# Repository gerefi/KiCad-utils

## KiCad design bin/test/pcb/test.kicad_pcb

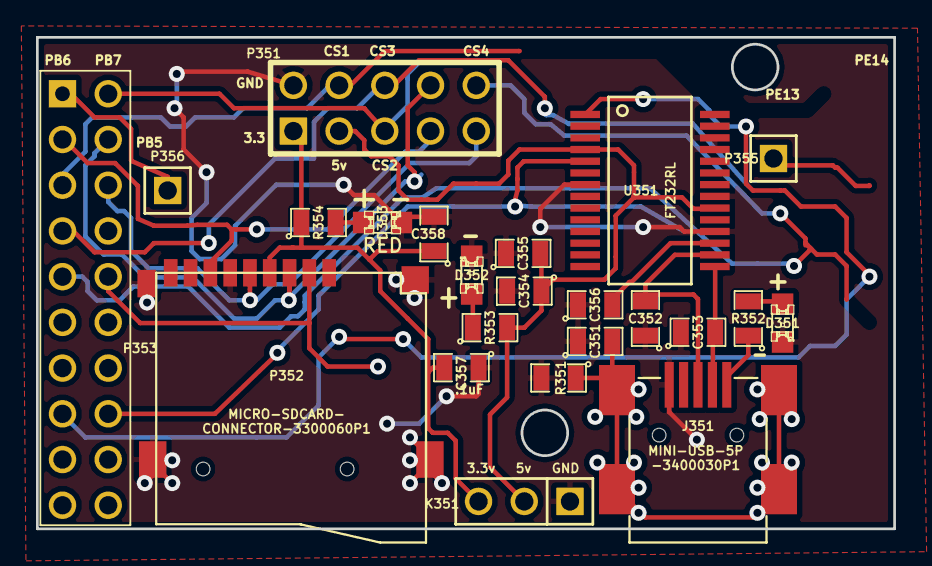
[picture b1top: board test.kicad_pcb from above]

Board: 2 copper layers, 47.6 x 27.3 mm, 24 parts (1 on the bottom side), 22 nets.

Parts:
C351: 4700pF; SM0805
C352, C353: 47pF; SM0805
C354, C358: 4.7uF; SM0805
C355, C356, C357: .1uF; SM0805
D351: GREEN; LED-0805
D352, D353: RED; LED-0805
G305: LOGO; LOGO_F
J351: MINI-USB-5P-3400020P1
K351: CONN_3; PIN_ARRAY_3_A
P351: CONN_5X2; PIN_ARRAY_5x2
P352: MICRO-SDCARD-CONNECTOR-3300060P1
P353: CONN_10X2; PIN_ARRAY_10X2
P355, P356: CONN_1; PIN_ARRAY_1
R351: 1M; SM0805
R352, R353, R354: 1k; SM0805
U351: FT232RL; ssop-28

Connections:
/3.3V: C357.2, C358.1, K351.3, P351.1, P352.4, R354.1
/5V: C354.1, C355.2, K351.2, P351.3, R353.2, U351.4, U351.20
/CAN_TX: P353.1, P356.1
/CS1: P351.4, P353.5
/CS2: P351.5, P353.2
/CS3: P351.6, P353.7
/CS4: P351.10, P353.9
/CS_SD_MODULE: P352.2, P353.10
/SPI_MISO: P351.7, P352.7, P353.3
/SPI_MOSI: P351.8, P352.3, P353.4
/SPI_SCK: P351.9, P352.5, P353.6
/USART_RX: P353.16, U351.5
/USART_TX: P353.15, U351.1
GND: C351.1, C352.1, C353.1, C354.2, C355.1, C356.1, C357.1, C358.2, D351.2, D352.2, D353.2, J351.5, K351.1, P351.2, P352.6, P352.G301, P352.G302, P352.G303, P352.G304, R351.2, U351.7, U351.18, U351.21, U351.25, U351.26
unnamed: J351.1, R352.1
unnamed: C351.2, J351.6, R351.1
unnamed: C353.2, J351.2, U351.15
unnamed: D351.1, R352.2
unnamed: C356.2, U351.17
unnamed: D352.1, R353.1
unnamed: C352.2, J351.3, U351.16
unnamed: D353.1, R354.2

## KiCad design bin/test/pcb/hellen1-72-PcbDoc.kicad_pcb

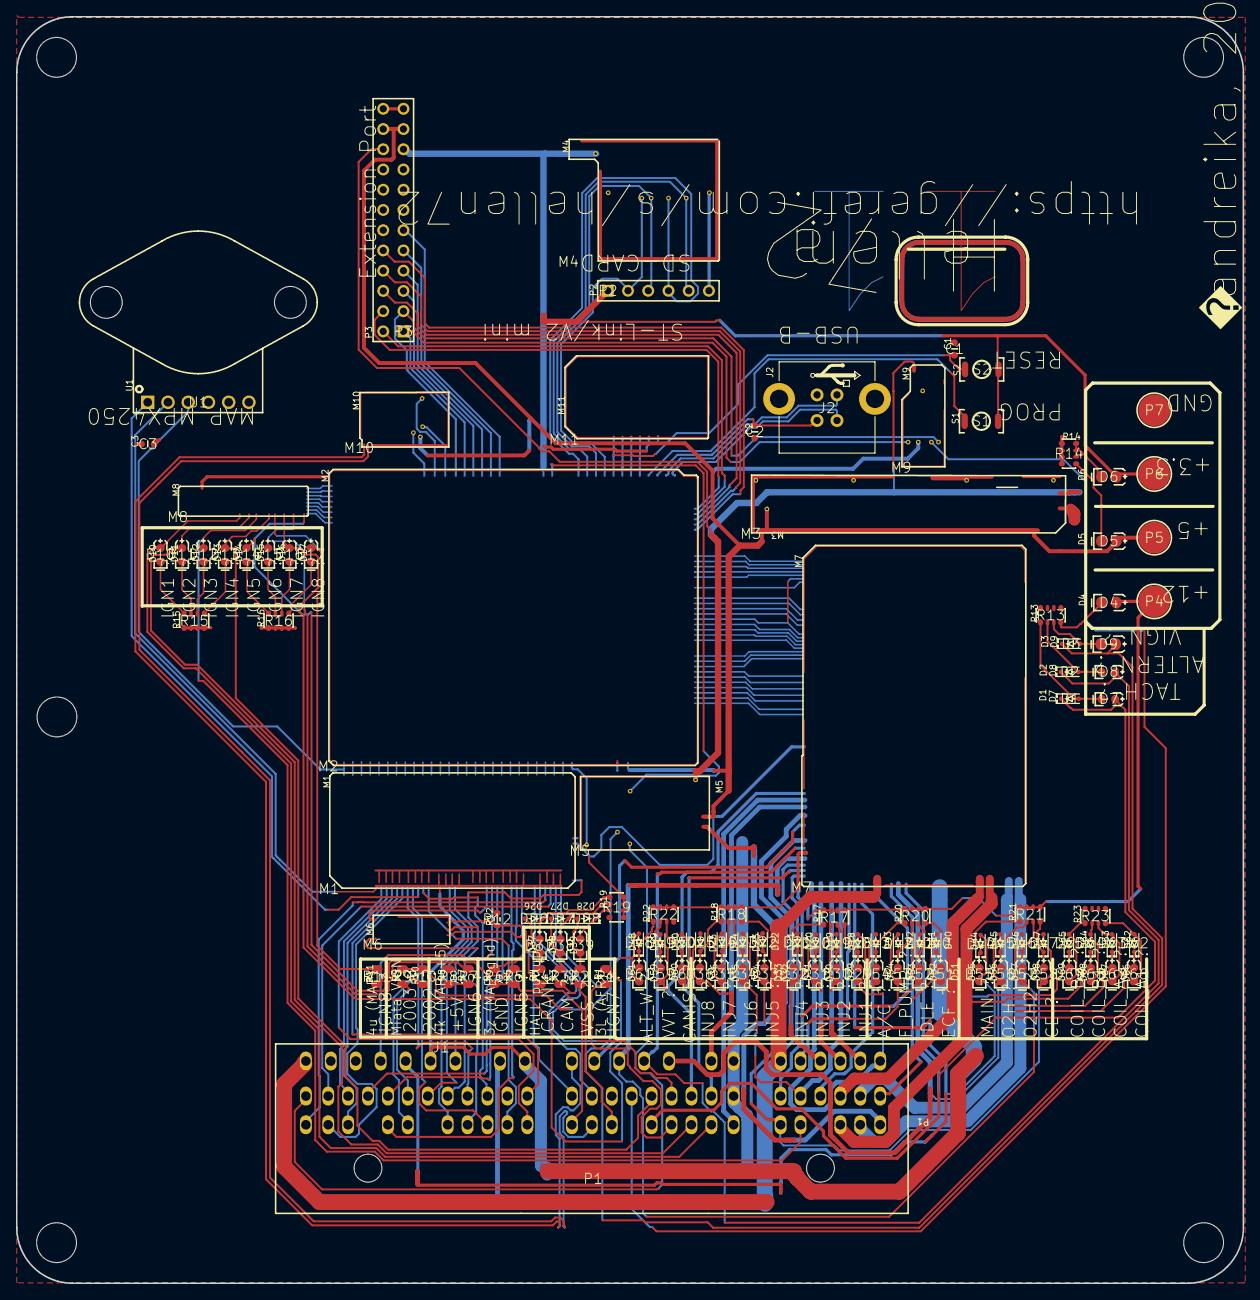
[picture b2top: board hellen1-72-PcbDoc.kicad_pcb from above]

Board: 2 copper layers, 154.0 x 159.0 mm, 118 parts (0 on the bottom side), 204 nets.

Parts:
C1: C1; C0603
C2: C2; C0603
C3: C3; C0603
D1: D1; SOD-323
D2: D2; SOD-323
D3: D3; SOD-323
D4: D4; LED-0805
D5: D5; LED-0805
D6: D6; LED-0805
D7: D7; LED-0603
D8: D8; LED-0603
D9: D9; LED-0805
D10: D10; LED-0603
D11: D11; LED-0603
D12: D12; LED-0603
D13: D13; LED-0603
D14: D14; LED-0603
D15: D15; LED-0603
D16: D16; LED-0603
D17: D17; LED-0603
D18: D18; SOD-323
D19: D19; SOD-323
D20: D20; SOD-323
D21: D21; SOD-323
D22: D22; SOD-323
D23: D23; SOD-323
D24: D24; SOD-323
D25: D25; SOD-323
D26: D26; SOD-323
D27: D27; SOD-323
D28: D28; SOD-323
D29: D29; LED-0603
D30: D30; LED-0603
D31: D31; LED-0603
D32: D32; LED-0603
D33: D33; LED-0603
D34: D34; LED-0603
D35: D35; LED-0603
D36: D36; LED-0603
D37: D37; LED-0603
D38: D38; LED-0603
D39: D39; LED-0603
D40: D40; SOD-323
D41: D41; SOD-323
D42: D42; SOD-323
D43: D43; SOD-323
D44: D44; SOD-323
D45: D45; SOD-323
D46: D46; SOD-323
D47: D47; SOD-323
D48: D48; SOD-323
D49: D49; SOD-323
D50: D50; SOD-323
D51: D51; LED-0603
D52: D52; LED-0603
D53: D53; LED-0603
D54: D54; LED-0603
D55: D55; LED-0603
D56: D56; LED-0603
D57: D57; LED-0603
D58: D58; LED-0603
D59: D59; LED-0603
D60: D60; LED-0603
D61: D61; LED-0603
D62: D62; SOD-323
D63: D63; SOD-323
D64: D64; SOD-323
D65: D65; SOD-323
D66: D66; LED-0603
D67: D67; LED-0603
D68: D68; LED-0603
D69: D69; LED-0603
J1: J1; NET-TIE
J2: J2; CONN-USB-B-VERTICAL
M1: M1; MOD_Hellen_Input
M2: M2; MOD_Hellen_MCU
M3: M3; MOD_Hellen_POWER_5
M4: M4; MOD_HELLEN_SD
M5: M5; MOD_Hellen_POWER_12
M6: M6; MOD_Hellen_Knock
M7: M7; MOD_Hellen_OUTPUT
M8: M8; MOD_Hellen_IGN8
M9: M9; MOD_Hellen_LIN
M10: M10; MOD_Hellen_CAN
M11: M11; MOD_HELLEN_STLINK
P1: P1; CONN-TE-72-PIN
P2: P2; HDR1X6
P3: P3; HDR2X12
P4: P4; PAD-SMD-4.0
P5: P5; PAD-SMD-4.0
P6: P6; PAD-SMD-4.0
P7: P7; PAD-SMD-4.0
R1: R1; R0805
R2: R2; R0805
R3: R3; R0805
R4: R4; R0805
R5: R5; R0805
R6: R6; R0805
R7: R7; R0805
R8: R8; R0805
R9: R9; R0805
R10: R10; R0805
R11: R11; R0805
R12: R12; R0603
R13: R13; R0603_x4
R14: R14; R0603_x4
R15: R15; R0603_x4
R16: R16; R0603_x4
R17: R17; R0603_x4
R18: R18; R0603_x4
R19: R19; R0603_x4
R20: R20; R0603_x4
R21: R21; R0603_x4
R22: R22; R0603_x4
R23: R23; R0603_x4
S1: S1; BUTTON-SKRK
S2: S2; BUTTON-SKRK
U1: U1; MPX4250AP

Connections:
AC: M2.E9, M7.W37
AC_PRESS: M1.N10, M2.S24
AFR: M1.N26, M2.S8
ALTERN: M2.E19, M7.W28
ALT_WARN: M2.E7, M7.W39
BOOT0: M2.N26, S1.1
BRAKE: M1.N6, M2.S28
CAM: M1.N19, M2.S15
CAM_PULLUP: D27.2, D38.2, R3.2
CANIST: M2.E21, M7.W26
CAN_N: M10.S1, P1.3X
CAN_P: M10.S2, P1.3W
CAN_RX: M2.N2, M10.V6
CAN_TX: M2.N3, M10.V5
CAN_VIO: M2.N1, M10.V2
CE: M2.E22, M7.W25
CLT: M1.N16, M2.S18
CLUTCH: M1.N8, M2.S26
COIL_A1: M2.E14, M7.W33
COIL_A2: M2.E15, M7.W32
COIL_B1: M2.E16, M7.W31
COIL_B2: M2.E17, M7.W30
CRANK: M1.N21, M2.S13
CRANK_PULLUP: D26.2, D37.2, R4.2
ECF: M2.E28, M7.W21
EGR: M1.N11, M2.S23
EXT_IO1: M2.N6, P3.5
EXT_IO2: M2.N7, P3.7
EXT_IO3: M2.N8, P3.9
EXT_IO4: M2.N9, P3.11
EXT_SPI_CS1: M2.E4, P3.8
EXT_SPI_CS2: M2.E5, P3.10
EXT_SPI_MISO: M2.E2, P3.2
EXT_SPI_MOSI: M2.E3, P3.6
EXT_SPI_SCK: M2.E1, P3.4
FTP_PPS: M1.N5, M2.S29
FUEL_LEVEL: M1.N24, M2.S10
GND: C1.2, C2.1, J1.1, J2.4, M1.E1, M1.E5, M2.S2, M3.E1, M3.V1, M3.V2, M3.V3, M3.V4, M4.G, M4.V2, M4.V3, M5.S1, M7.G, M7.S3, M8.G, M9.E1, M9.S1, M10.E1, M11.G, P1.3A, P1.3B, P1.4A, P2.6, P3.23, P3.24, P7.1, R13.5, R13.6, R13.7, R13.8, R14.5, R14.6, R14.7, R14.8, R15.5, R15.6, R15.7, R15.8, R16.5, R16.6, R16.7, R16.8, R23.5, R23.6, R23.7, R23.8
GNDA: C3.2, J1.2, M1.J2, M1.J11, M1.J12, M1.J13, M1.J14, M1.J22, M1.J23, M1.J25, M1.J26, M1.N2, M2.S32, M6.E1, P1.4O, R6.2, R12.1, U1.2
IAT: M1.N15, M2.S19
IDLE: M2.E18, M7.W29, M7.W35
IGN1: M2.W1, M8.E8
IGN2: M2.W2, M8.E7
IGN3: M2.W3, M8.E6
IGN4: M2.W4, M8.E5
IGN5: M2.W5, M8.E4
IGN6: M2.W6, M8.E3
IGN7: M2.W7, M8.E2
IGN8: M2.W8, M8.E1
INJ1: M2.E25, M7.W24
INJ2: M2.E26, M7.W23
INJ3: M2.E29, M7.W20
INJ4: M2.E30, M7.W19
INJ5: M2.E31, M7.W18
INJ6: M2.E32, M7.W17
INJ7: M2.E33, M7.W16
INJ8: M2.E34, M7.W15
IN_AC_PRESS: M1.S17, P1.4F
IN_AFR: M1.S1, P1.3L, R1.1
IN_BRAKE: M1.S23, P1.4B
IN_CAM: M1.S5, P1.3V, R3.1
IN_CLT: M1.S15, P1.4P
IN_CLUTCH: M1.S20, P1.4I
IN_CRANK: M1.S8, P1.3Y, R4.1
IN_EGR: M1.S22, P1.4AE
IN_FTP_PPS: M1.S24, P1.4AB
IN_FUEL_LEVEL: M1.S3, P1.4AD
IN_IAT: M1.S16, P1.4N
IN_KNOCK: M1.S7, M6.E3
IN_KNOCK_RAW: M6.W1, P1.4M
IN_MAF: M1.S11, P1.4X, R12.2
IN_MAP2: M1.S12, P1.4U, R11.1
IN_MAP3: M1.S19, U1.1
IN_NEUTRAL: M1.S18, P1.4H
IN_O2S: M1.S9, P1.4W
IN_O2S2: M1.S25, P1.4AA
IN_SENS2: M1.S2, P1.3K
IN_SENS4: M1.S4, P1.4AH
IN_STEERING: M1.S26, P1.4C
IN_TPS: M1.S10, P1.4V
IN_VIGN: D3.1, D9.1, M5.V3, R9.2, R10.2
IN_VSS: M1.S6, P1.3T, R2.1
IN_VTCS: M1.S21, P1.4J
KNOCK: M1.N22, M2.S12
LIN: M9.V4, P1.3Q
MAF: M1.N14, M2.S20
MAIN: M2.E6, M7.W40
MAP2: M1.N13, M2.S21
MAP3: M1.N12, M2.S22
NEUTRAL: M1.N9, M2.S25
NetD1_2: D1.2, D7.2, R13.1
NetD2_2: D2.2, D8.2, R13.2
NetD3_2: D3.2, D9.2, R13.3
NetD4_2: D4.2, R13.4
NetD5_2: D5.2, R14.1
NetD6_2: D6.2, R14.2, R14.3, R14.4
NetD10_2: D10.2, R15.4
NetD11_2: D11.2, R15.3
NetD12_2: D12.2, R15.2
NetD13_2: D13.2, R15.1
NetD14_2: D14.2, R16.4
NetD15_2: D15.2, R16.3
NetD16_2: D16.2, R16.2
NetD17_2: D17.2, R16.1
NetD18_1: D18.1, D29.1, R17.4
NetD19_1: D19.1, D30.1, R17.3
NetD20_1: D20.1, D31.1, R17.2
NetD21_1: D21.1, D32.1, R17.1
NetD22_1: D22.1, D33.1, R18.4
NetD23_1: D23.1, D34.1, R18.3
NetD24_1: D24.1, D35.1, R18.2
NetD25_1: D25.1, D36.1, R18.1
NetD26_1: D26.1, D37.1, R19.1
NetD27_1: D27.1, D38.1, R19.2
NetD28_1: D28.1, D39.1, R19.3
NetD40_1: D40.1, D51.1, R20.4
NetD41_1: D41.1, D52.1, R20.3
NetD42_1: D42.1, D53.1, R20.2
NetD43_1: D43.1, D54.1, R20.1
NetD44_1: D44.1, D55.1, R21.1
NetD45_1: D45.1, D56.1, R21.2
NetD46_1: D46.1, D57.1, R21.3
NetD47_1: D47.1, D58.1, R21.4
NetD48_1: D48.1, D61.1, R22.1
NetD49_1: D49.1, D59.1, R22.2
NetD50_1: D50.1, D60.1, R22.3
NetD62_2: D62.2, D66.2, R23.4
NetD63_2: D63.2, D67.2, R23.3
NetD64_2: D64.2, D68.2, R23.2
NetD65_2: D65.2, D69.2, R23.1
NetP1_3Z: P1.3Z, R5.1, R6.1
NetP1_4K: P1.4K, R7.1, R8.1
NetP1_4S: P1.4S, R9.1
NetP1_4T: P1.4T, R10.1
O2H: M2.E8, M7.W38
O2H2: M2.E12, M7.W34
O2S: M1.N18, M2.S16
O2S2: M1.N4, M2.S30
OUT_AC: D43.2, D54.2, M7.S12, P1.2K
OUT_ALTERN: D2.1, D8.1, M7.W6, P1.3M
OUT_ALT_WARN: D48.2, D61.2, M7.W9, P1.3U
OUT_CANIST: D50.2, D60.2, M7.W2, P1.3E
OUT_CE: D47.2, D58.2, M7.W3, P1.2R
OUT_COIL_A1: D62.1, D66.1, M7.S1, P1.2F
OUT_COIL_A2: D63.1, D67.1, M7.S2, P1.2E
OUT_COIL_B1: D64.1, D68.1, M7.S4, P1.2I
OUT_COIL_B2: D65.1, D69.1, M7.S5, P1.2H
OUT_ECF: D40.2, D51.2, M7.S8, P1.2B
OUT_IDLE: D41.2, D52.2, M7.S10, M7.W1, P1.2Q
OUT_IGN1: D10.1, M8.S8, P1.3F
OUT_IGN2: D11.1, M8.S7, P1.3I
OUT_IGN3: D12.1, M8.S6, P1.2O
OUT_IGN4: D13.1, M8.S5, P1.3N
OUT_IGN5: D14.1, M8.S1, R5.2
OUT_IGN6: D15.1, M8.S2, R7.2
OUT_IGN7: D16.1, M8.S3, R1.2
OUT_IGN8: D17.1, M8.S4, R11.2
OUT_INJ1: D18.2, D29.2, M7.S18, P1.2A
OUT_INJ2: D19.2, D30.2, M7.S16, P1.2D
OUT_INJ3: D20.2, D31.2, M7.S17, P1.2G
OUT_INJ4: D21.2, D32.2, M7.W7, P1.2J
OUT_INJ5: D22.2, D33.2, M7.W10, P1.2C
OUT_INJ6: D23.2, D34.2, M7.S15, P1.2N
OUT_INJ7: D24.2, D35.2, M7.W12, P1.3C
OUT_INJ8: D25.2, D36.2, M7.W11, P1.3D
OUT_MAIN: D49.2, D59.2, M7.W13, P1.3H
OUT_O2H: D45.2, D56.2, M7.S7, P1.3J
OUT_O2H2: D46.2, D57.2, M7.W4, P1.3P
OUT_PUMP: D42.2, D53.2, M7.S14, P1.2M
OUT_TACH: D1.1, D7.1, M7.S6, P1.3O
OUT_VVT: D44.2, D55.2, M7.S13, P1.4R
PUMP: M2.E20, M7.W27
SD_CS: M2.N21, M4.V4, P2.2
SD_MISO: M2.N19, M4.V7, P2.5
SD_MOSI: M2.N20, M4.V5, P2.3
SD_SCK: M2.N18, M4.V6, P2.4
SENS2: M1.N25, M2.S9
SENS4: M1.N23, M2.S11
STEERING: M1.N3, M2.S31
SWCLK: M2.N23, M11.N5
SWDIO: M2.N24, M11.N4
SWO: M2.N25, M11.N3
TACH: M2.E27, M7.W22
TPS: M1.N17, M2.S17
UART_RX: M2.N5, M9.V2, P3.1
UART_TX: M2.N4, M9.V5, P3.3
USB_N: J2.2, M2.N29
USB_P: J2.3, M2.N28
V5: D5.1, M1.E2, M2.S1, M3.V6, M5.E1, M7.W14, M9.V3, M10.V1, M11.N1, P3.21, P3.22, P5.1, R19.5, R19.6, R19.7, R19.8
V5A: C3.1, M1.E6, M1.J1, M1.J3, M1.J4, M1.J5, M1.J6, M1.J7, M1.J8, M1.J9, M1.J10, M1.J15, M1.J16, M1.J17, M1.J18, M1.J19, M1.J20, M1.J21, M1.J24, M1.N1, M2.S33, M6.E2, P1.4L, R8.2, U1.3
V12: M3.V5, M5.V1, M9.N1, M9.V1, P3.20
V12P: D4.1, M7.W5, P4.1, R17.5, R17.6, R17.7, R17.8, R18.5, R18.6, R18.7, R18.8, R20.5, R20.6, R20.7, R20.8, R21.5, R21.6, R21.7, R21.8, R22.5, R22.6, R22.7, R22.8
V12_PERM: M5.V4, P1.4AG
V12_RAW: M5.E2, M7.S11, P1.2P, P1.4AF, P1.4D
V33: D6.1, M2.N14, M4.V1, M11.N2, P2.1, P3.19, P6.1, S1.2, S2.2
VBAT: M2.N15, M5.V2
VBUS: C2.2, J2.1, M2.N27
VIGN: M2.S7, M5.V5
VREF2: M1.S13, M6.W2
VSS: M1.N20, M2.S14
VSS_PULLUP: D28.2, D39.2, R2.2
VTCS: M1.N7, M2.S27
VVT: M2.E10, M7.W36
nReset: C1.1, M2.N22, M11.N6, S2.1

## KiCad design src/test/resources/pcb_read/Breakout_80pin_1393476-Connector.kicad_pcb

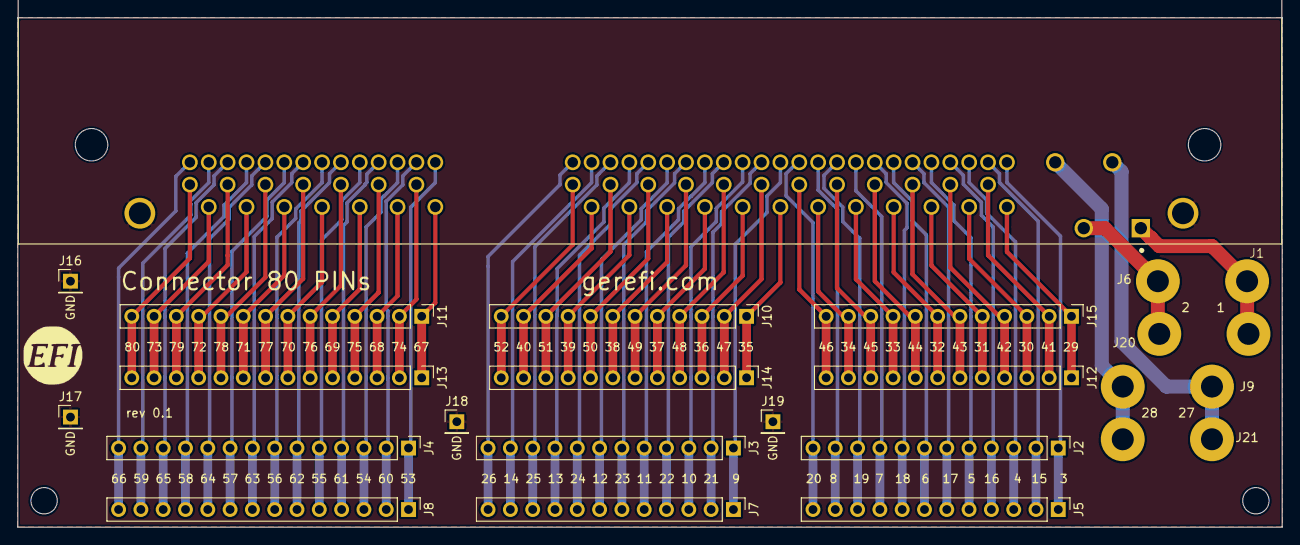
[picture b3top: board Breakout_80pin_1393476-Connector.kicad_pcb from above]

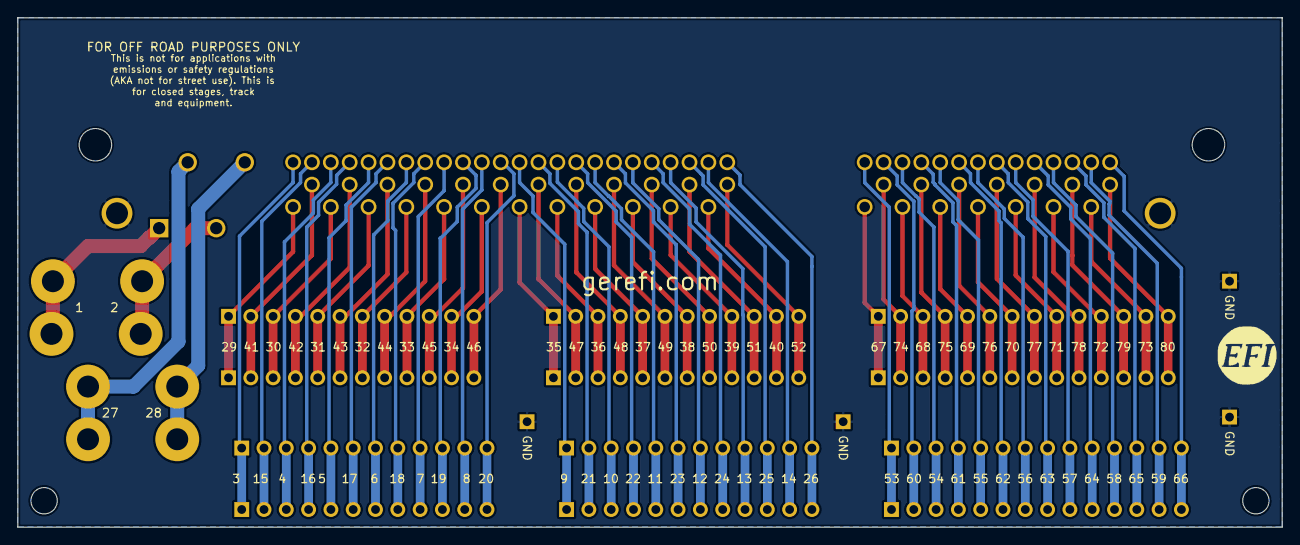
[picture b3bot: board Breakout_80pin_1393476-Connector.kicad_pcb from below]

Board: 2 copper layers, 144.0 x 58.0 mm, 24 parts (2 on the bottom side), 81 nets.

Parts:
G?: Disclaimer; Off_Road_Disclaimer
G?#2, G?#3: LOGO
J1: 8-1393476-0
J2, J3, J5, J7, J10, J12, J14, J15: Conn_01x12; Pin_Header_Straight_1x12_Pitch2.54mm
J4, J8, J11, J13: Conn_01x14; Pin_Header_Straight_1x14_Pitch2.54mm
J6, J9, J20, J21: Screw_Terminal_01x02; WireConnection_2.50mmDrill
J16, J17, J18, J19: Conn_01x01; Pin_Header_Straight_1x01_Pitch2.54mm

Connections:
Earth: J1.81, J1.82, J16.1, J17.1, J18.1, J19.1
unnamed: J1.1, J6.1, J20.1
unnamed: J1.2, J6.2, J20.2
unnamed: J1.3, J2.1, J5.1
unnamed: J1.4, J2.3, J5.3
unnamed: J1.5, J2.5, J5.5
unnamed: J1.6, J2.7, J5.7
unnamed: J1.7, J2.9, J5.9
unnamed: J1.8, J2.11, J5.11
unnamed: J1.9, J3.1, J7.1
unnamed: J1.10, J3.3, J7.3
unnamed: J1.11, J3.5, J7.5
unnamed: J1.12, J3.7, J7.7
unnamed: J1.13, J3.9, J7.9
unnamed: J1.14, J3.11, J7.11
unnamed: J1.15, J2.2, J5.2
unnamed: J1.16, J2.4, J5.4
unnamed: J1.17, J2.6, J5.6
unnamed: J1.18, J2.8, J5.8
unnamed: J1.19, J2.10, J5.10
unnamed: J1.20, J2.12, J5.12
unnamed: J1.21, J3.2, J7.2
unnamed: J1.22, J3.4, J7.4
unnamed: J1.23, J3.6, J7.6
unnamed: J1.24, J3.8, J7.8
unnamed: J1.25, J3.10, J7.10
unnamed: J1.26, J3.12, J7.12
unnamed: J1.27, J9.1, J21.1
unnamed: J1.28, J9.2, J21.2
unnamed: J1.29, J12.1, J15.1
unnamed: J1.30, J12.3, J15.3
unnamed: J1.31, J12.5, J15.5
unnamed: J1.32, J12.7, J15.7
unnamed: J1.33, J12.9, J15.9
unnamed: J1.34, J12.11, J15.11
unnamed: J1.35, J10.1, J14.1
unnamed: J1.36, J10.3, J14.3
unnamed: J1.37, J10.5, J14.5
unnamed: J1.38, J10.7, J14.7
unnamed: J1.39, J10.9, J14.9
unnamed: J1.40, J10.11, J14.11
unnamed: J1.41, J12.2, J15.2
unnamed: J1.42, J12.4, J15.4
unnamed: J1.43, J12.6, J15.6
unnamed: J1.44, J12.8, J15.8
unnamed: J1.45, J12.10, J15.10
unnamed: J1.46, J12.12, J15.12
unnamed: J1.47, J10.2, J14.2
unnamed: J1.48, J10.4, J14.4
unnamed: J1.49, J10.6, J14.6
unnamed: J1.50, J10.8, J14.8
unnamed: J1.51, J10.10, J14.10
unnamed: J1.52, J10.12, J14.12
unnamed: J1.53, J4.1, J8.1
unnamed: J1.54, J4.3, J8.3
unnamed: J1.55, J4.5, J8.5
unnamed: J1.56, J4.7, J8.7
unnamed: J1.57, J4.9, J8.9
unnamed: J1.58, J4.11, J8.11
unnamed: J1.59, J4.13, J8.13
unnamed: J1.60, J4.2, J8.2
unnamed: J1.61, J4.4, J8.4
unnamed: J1.62, J4.6, J8.6
unnamed: J1.63, J4.8, J8.8
unnamed: J1.64, J4.10, J8.10
unnamed: J1.65, J4.12, J8.12
unnamed: J1.66, J4.14, J8.14
unnamed: J1.67, J11.1, J13.1
unnamed: J1.68, J11.3, J13.3
unnamed: J1.69, J11.5, J13.5
unnamed: J1.70, J11.7, J13.7
unnamed: J1.71, J11.9, J13.9
unnamed: J1.72, J11.11, J13.11
unnamed: J1.73, J11.13, J13.13
unnamed: J1.74, J11.2, J13.2
unnamed: J1.75, J11.4, J13.4
unnamed: J1.76, J11.6, J13.6
unnamed: J1.77, J11.8, J13.8
unnamed: J1.78, J11.10, J13.10
unnamed: J1.79, J11.12, J13.12
unnamed: J1.80, J11.14, J13.14

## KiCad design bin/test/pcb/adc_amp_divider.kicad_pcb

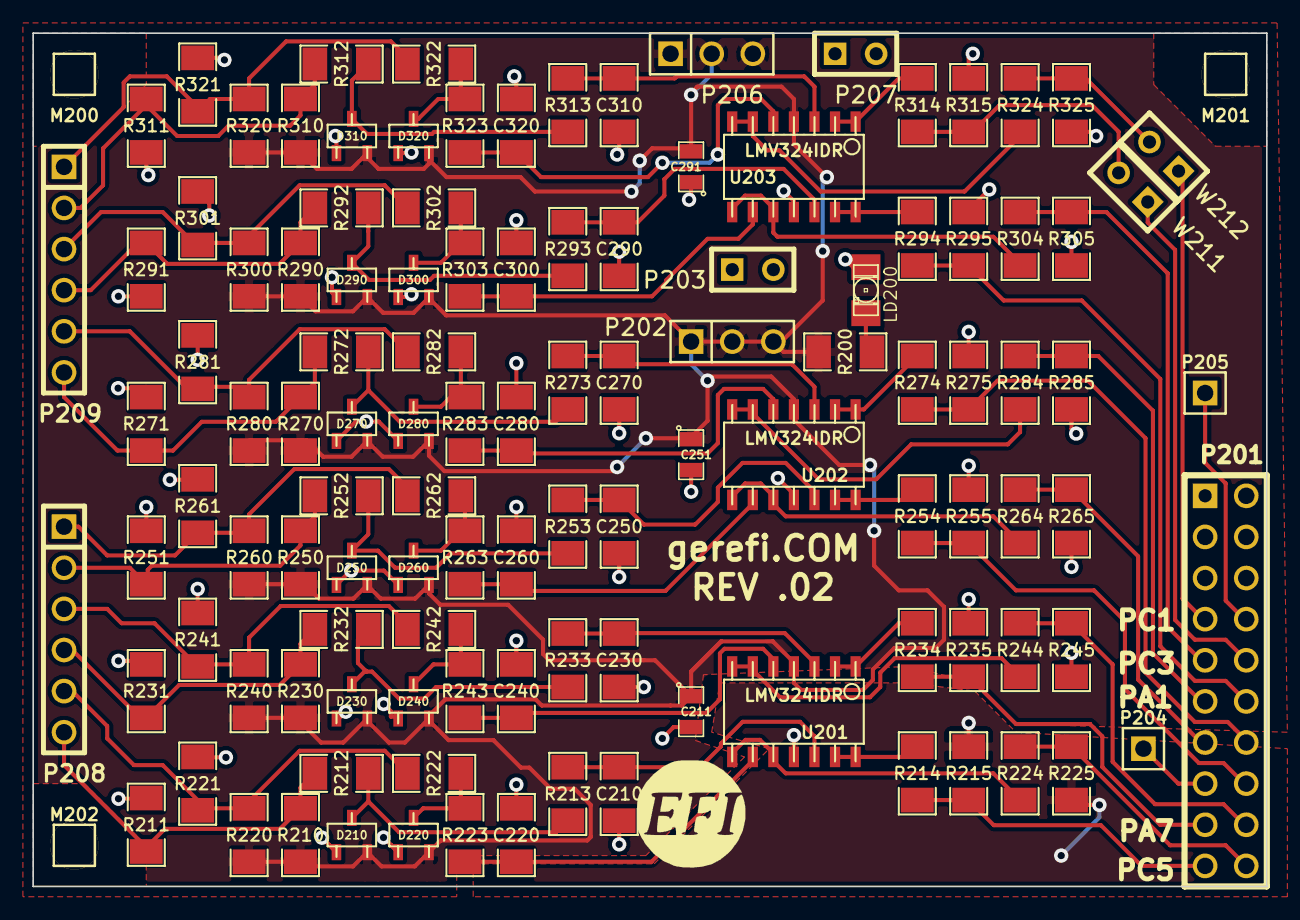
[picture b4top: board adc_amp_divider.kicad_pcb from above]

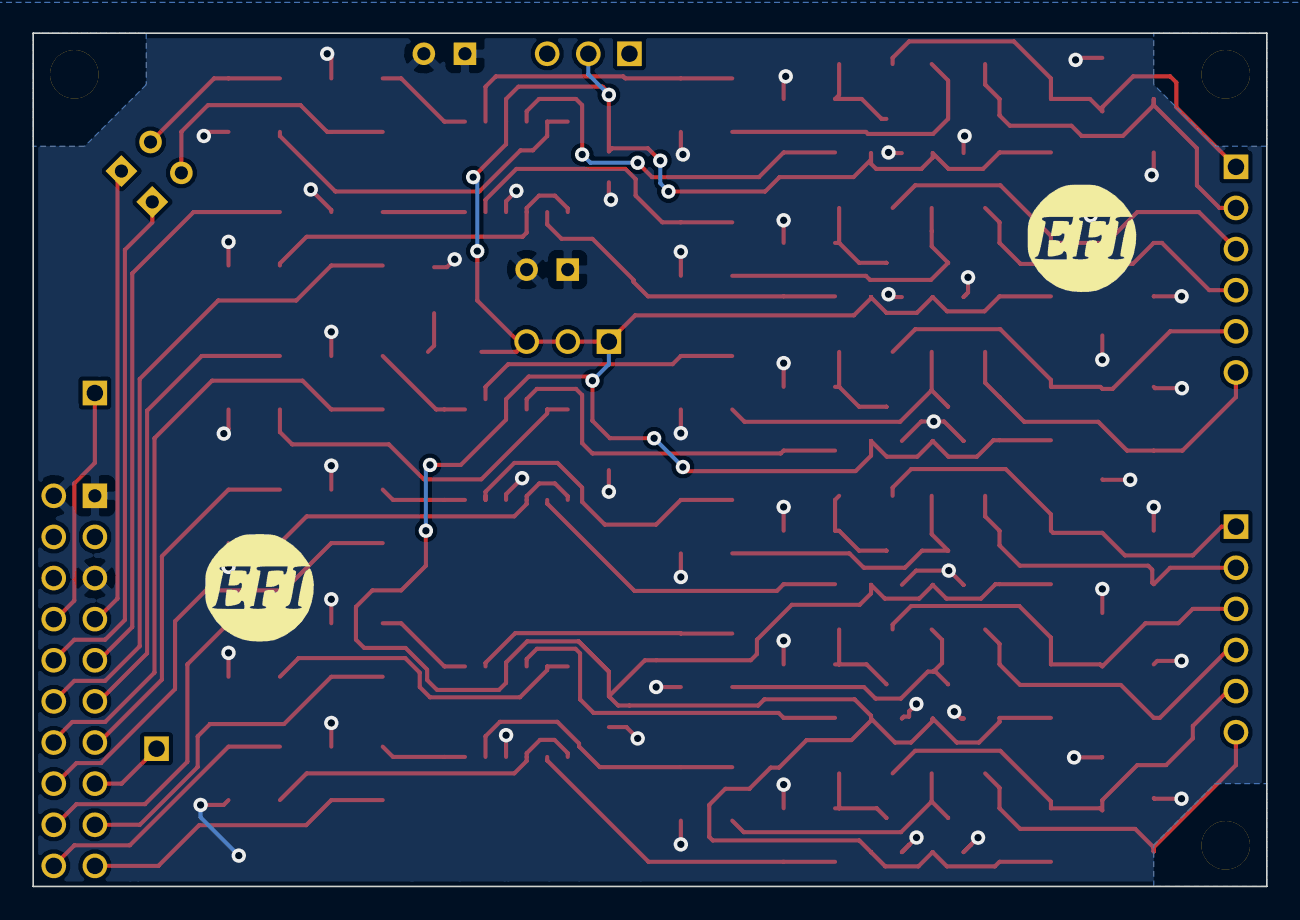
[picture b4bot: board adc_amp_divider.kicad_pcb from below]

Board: 2 copper layers, 76.2 x 52.7 mm, 121 parts (2 on the bottom side), 67 nets.

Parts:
C210, C220, C230, C240, C250, C260, C270, C280, C290, C300, C310, C320: 0.01uF; SM1206
C211, C251, C291: 0.1uF; SM0805
D210, D220, D230, D240, D250, D260, D270, D280, D290, D300, D310, D320: DOUBLE_SCHOTTKY; sot23
G200: LOGO
G201, G202: LOGO; LOGO_F
LD200: LED; LED-1206
M200, M201, M202: CONN_1; PIN_ARRAY_1
P201: CONN_10X2; PIN_ARRAY_10X2
P202, P206: CONN_3; PIN_ARRAY_3X1
P203, P207: CONN_2; SIL-2
P204, P205: CONN_1; PIN_ARRAY_1
P208, P209: CONN_6; PIN_ARRAY-6X1
R200, R213, R223, R233, R243, R253, R263, R273, R283, R293, R303, R313, R323: 100; SM1206
R210, R220, R230, R240, R250, R260, R270, R280, R290, R300, R310, R320: 2700; SM1206
R211, R221, R231, R241, R251, R261, R271, R281, R291, R301, R311, R321: 500K; SM1206
R212, R222, R232, R242, R252, R262, R272, R282, R292, R302, R312, R322: 10k; SM1206
R214, R215, R224, R225, R234, R235, R244, R245, R254, R255, R264, R265, R274, R275, R284, R285, R294, R295, R304, R305, R314, R315, R324, R325: 1500; SM1206
U201, U202, U203: LMV324IDR; so-14
W211, W212: TEST; SIL-2

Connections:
/INP1: P208.6, R210.1, R211.1, R212.1
/INP2: P208.5, R220.1, R221.1, R222.1
/INP3: P208.4, R230.1, R231.1, R232.1
/INP4: P208.3, R240.1, R241.1, R242.1
/INP5: P208.2, R250.1, R251.1, R252.1
/INP6: P208.1, R260.1, R261.1, R262.1
/INP7: P209.6, R270.1, R271.1, R272.1
/INP8: P209.5, R280.1, R281.1, R282.1
/INP9: P209.4, R290.1, R291.1, R292.1
/INP10: P209.3, R300.1, R301.1, R302.1
/INP11: P209.2, R310.1, R311.1, R312.1
/INP12: P209.1, R320.1, R321.1, R322.1
/OUT1: P201.19, R214.2, R215.1
/OUT2: P201.20, R224.2, R225.1
/OUT3: P201.17, R234.2, R235.1
/OUT4: P201.18, R244.2, R245.1
/OUT5: P201.16, R254.2, R255.1
/OUT6: P201.13, R264.2, R265.1
/OUT7: P201.14, R274.2, R275.1
/OUT8: P201.11, R284.2, R285.1
/OUT9: P201.12, R294.2, R295.1
/OUT10: P201.9, R304.2, R305.1
/OUT11: P201.10, W211.1
/OUT12: P201.7, W212.1
/PA5: P201.15, P204.1
/PC0: P201.8, P205.1
GND: C210.1, C211.2, C220.1, C230.1, C240.1, C250.1, C251.2, C260.1, C270.1, C280.1, C290.1, C291.1, C300.1, C310.1, C320.1, D210.1, D220.1, D230.1, D240.1, D250.1, D260.1, D270.1, D280.1, D290.1, D300.1, D310.1, D320.1, LD200.1, P201.1, P201.2, P201.5, P203.1, P203.2, P207.1, P207.2, R211.2, R215.2, R221.2, R225.2, R231.2, R235.2, R241.2, R245.2, R251.2, R255.2, R261.2, R265.2, R271.2, R275.2, R281.2, R285.2, R291.2, R295.2, R301.2, R305.2, R311.2, R315.2, R321.2, R325.2, U201.11, U202.11, U203.11
unnamed: D210.2, R212.2, R213.1
unnamed: D220.2, R222.2, R223.1
unnamed: C290.2, R293.2, U203.12
unnamed: C300.2, R303.2, U203.9
unnamed: D290.2, R292.2, R293.1
unnamed: D280.2, R282.2, R283.1
unnamed: D270.2, R272.2, R273.1
unnamed: D250.2, R252.2, R253.1
unnamed: D260.2, R262.2, R263.1
unnamed: D300.2, R302.2, R303.1
unnamed: R294.1, U203.13, U203.14
unnamed: R304.1, U203.8, U203.10
unnamed: C320.2, R323.2, U203.5
unnamed: D320.2, R322.2, R323.1
unnamed: D310.2, R312.2, R313.1
unnamed: R314.1, U203.1, U203.2
unnamed: C310.2, R313.2, U203.3
unnamed: R324.1, U203.6, U203.7
unnamed: R324.2, R325.1, W212.2
unnamed: R314.2, R315.1, W211.2
unnamed: R284.1, U202.6, U202.7
unnamed: R274.1, U202.1, U202.2
unnamed: R264.1, U202.8, U202.10
unnamed: R214.1, U201.13, U201.14
unnamed: R224.1, U201.8, U201.10
unnamed: R234.1, U201.1, U201.2
unnamed: R244.1, U201.6, U201.7
unnamed: C250.2, R253.2, U202.12
unnamed: R254.1, U202.13, U202.14
unnamed: C240.2, R243.2, U201.5
unnamed: D240.2, R242.2, R243.1
unnamed: C230.2, R233.2, U201.3
unnamed: C280.2, R283.2, U202.5
unnamed: C270.2, R273.2, U202.3
unnamed: C220.2, R223.2, U201.9
unnamed: C210.2, R213.2, U201.12
unnamed: C260.2, R263.2, U202.9
unnamed: LD200.2, R200.2
unnamed: D230.2, R232.2, R233.1
VCC: C211.1, C251.1, C291.2, D210.3, D220.3, D230.3, D240.3, D250.3, D260.3, D270.3, D280.3, D290.3, D300.3, D310.3, D320.3, P202.1, P202.2, P202.3, P206.1, P206.2, P206.3, R200.1, R210.2, R220.2, R230.2, R240.2, R250.2, R260.2, R270.2, R280.2, R290.2, R300.2, R310.2, R320.2, U201.4, U202.4, U203.4
